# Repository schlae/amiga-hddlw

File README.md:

# Herr Doktor Diskettenlaufwerk (Amiga-HDDLW)

Late-model Amiga computers use customized floppy drives (like the Chinon
FZ-357A) to be able to read and write high-density floppy disks
(colloquially known as 1.44MB floppies, although the Amiga can store 1.76MB
because it packs in four additional sectors per track.)

Why a customized floppy drive? The Amiga custom chip, Paula, only supports
the slower bit rate used by double-density floppy disks. Instead of spending
a bunch of money to change the Paula chip, Commodore engineers got a
customized floppy drive that spun the disk at half speed when it detected
a high-density floppy disk.

In the 1990s, some 3rd party vendors released Amiga compatible floppy drives.
One such design is the AMTRADE "The Real HD-Drive" A357. It uses a modified
Sony MPF920-E or a TEAC FD-235HF (both fairly common) along with a small
adapter circuit board containing a 16V8 PAL.

I've done a bit of reverse engineering to understand how the A357 works,
and I've been able to build a functional replica. It's not an exact copy
because the original PAL is locked. I'm calling it the Herr Doktor
Diskettenlaufwerk, or HDDLW.

*Please note that I have not fabbed out this design yet, and although the
design is tested and expected to work, go forward at your own risk.*

## Fabrication

The board is a simple 2-layer affair with a small handful of parts. The
dimensions are 93.5mm x 20.3mm (3.68" x 0.8").

[Schematic](https://github.com/schlae/amiga-hddlw/blob/main/amiga-hddlw.pdf)

[Bill of Materials](https://github.com/schlae/amiga-hddlw/blob/main/amiga-hddlw.csv)

[Fab Package](https://github.com/schlae/amiga-hddlw/blob/main/fab/amiga-hddlw_rev1.zip)

Install a 20-pin DIP socket in position U1 just in case you have trouble
programming the PAL. All parts, with the exception of J2, J5, and J6, should
be installed on the top side of the board.

J4 should be a Molex 4-pin header with a key. In a pinch, you can sub it out
with a standard 4-pin header but it will be very easy to connect the cable
backwards, which will put 12V on the drive's 5V rail, destroying everything!

Install **either** J5 **or** J6 depending on the drive you plan to use. If you
install both, J5 will interfere with the drive select jumpers on the Sony
drive and potentially damage them.

Jumper J3 should be set to 1 for DF0 and 2 for DF1. Position 3 has not been
tested yet but may work.

## Rework

You will (most likely) need to add a bodge resistor to the design for it to
operate properly on many drives. This is because the pullup on the INDEX line
on the drive itself is weak or nonexistent. Connect a 10K ohm resistor from
pin 7 of the PAL to pin 20 of the PAL.

(Bottom view of the board)

## PAL programming

See the [source file](https://github.com/schlae/amiga-hddlw/blob/main/pal/amiga-hddlw.pld).

The logic equations are assembled using [galette](https://github.com/simon-frankau/galette)
and can be burned to the PAL using a number of different tools. I use the
TL-866 with the [minipro](https://gitlab.com/DavidGriffith/minipro) tool under
Linux, along with the ATF16V8B. The speed grade is not critical.

## Drive modifications

The HDDLW has been tested with the two floppy drives below. It may be possible
to use it with other drives, but you will need to investigate to figure out
the clock connection that sets the motor RPM. You will also need to figure
out how to get the high density select signal onto pin 4 of the drive.

### Sony MPF920-E

Perform the following changes

* Install JC40 (a zero ohm resistor or wire jumper), which is connected to pin
4 of the floppy connector and provides the high-density sense signal. See the
green circle in the image below.
* Cut the trace between pin 38 of IC1 and pin 16 of IC2. This is the motor
driver clock. This is indicated by the diagonal arrow in the image below.
* Connect a wire from pin 38 of IC1 to pin 14 of the floppy connector (blue
wire in the image)
* Connect a wire from pin 16 of IC2 to pin 6 of the floppy connector (red
wire in the image)
* (Optional) This drive *may* have issues regulating the motor speed at lower RPMs. You can try changing resistor R21 (located next to IC2) from 100K to a 68K resistor.

### TEAC FD-235HF

Perform the following changes

* Install S5 (a zero ohm resistor or wire jumper), which is connected to pin 4
of the floppy connector and provides the high-density sense signal (circled in
the image)
* Remove 1K resistor R9 (which may be named differently on different board
revs, but one end is always tied to pin 4 of J5; pointed to by the green
arrow)
* Connect a wire from U1 pin 48 to pin 14 of the floppy connector
* Connect a wire from J5 pin 4 to pin 6 of the floppy connector

TEAC used several different board versions, so your board may not look exactly
alike. The example below uses R12 instead of R9, and S5 has been moved although
it retains the same designator.

Another alternative board uses R12 (as above) but uses S6 instead of S5.

## Functional Explanation

The drive modifications intercept the clock signal that goes between the
floppy drive's main control IC and the motor controller, bringing them out
to two unused pins on the floppy connector. They also enable the undocumented
feature that provides a high-density detect output on pin 4.

The PAL checks for high density disks by looking at pin 4. If a high density
disk is inserted, the PAL

* Divides the motor clock by 2 to slow the RPM from 300 to 150rpm
* Returns the drive ID pattern `10101010...` to the Amiga to let it know that
this is a high-density drive/disk.

If a double-density disk is inserted, the PAL

* Passes the motor clock signal through unchanged so the disk spins at 300rpm
* Returns the drive ID pattern `11111111...`, a double-density drive/disk

And that's about it.

## Troubleshooting

Some folks have issues where high density disks will sometimes read but will not format correctly. This can be caused by the motor speed not regulating well at the lower RPM. On the Sony drive, you can replace R21 with a 68K resistor. The TEAC drives may have similar problems but I haven't figured out a rework for them.

## License
This work is licensed under a Creative Commons Attribution-ShareAlike 4.0
International License. See [https://creativecommons.org/licenses/by-sa/4.0/](https://creativecommons.org/licenses/by-sa/4.0/).

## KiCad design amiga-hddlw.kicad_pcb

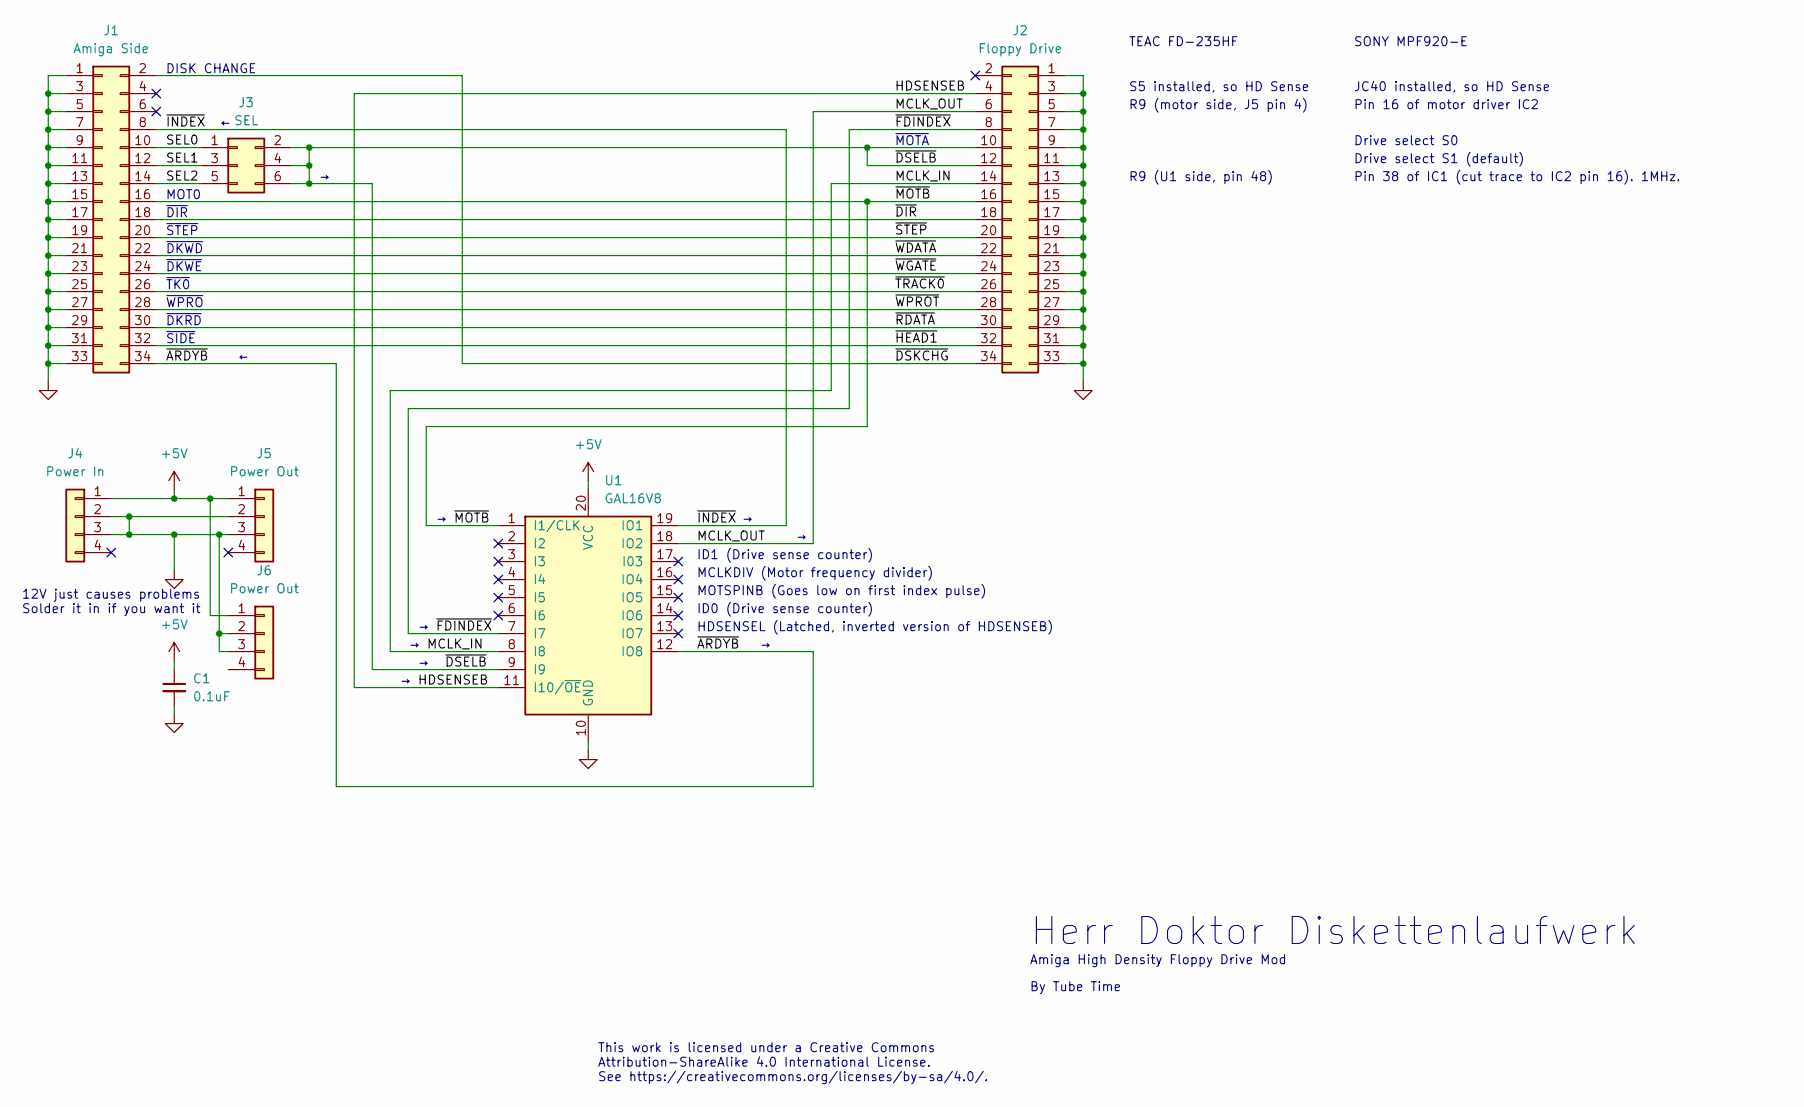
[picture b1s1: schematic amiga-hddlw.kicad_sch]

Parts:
C1: 0.1uF; CAPAC200; Mouser 594-K104K10X7RF53H5 or equiv
J1: Amiga Side; HEADER_2x17_254_SHROUDED; Mouser 737-BHR-34-VUA or equiv
J2: Floppy Drive; PinSocket_2x17_P2.54mm_Vertical; Mouser 517-929975-01-17-RK or equiv
J3: SEL; PinHeader_2x03_P2.54mm_Vertical; Mouser (Just use generic breakaway header)
J4: Power In; PinHeader_1x04_P2.54mm_Vertical; Mouser 571-1718254
J5: Power Out; PinSocket_1x04_P2.54mm_Vertical; Mouser 571-5-146763-6 or equiv
J6: Power Out; PinSocket_1x04_P2.54mm_Vertical
U1: GAL16V8; DIP254P762X635-20; Mouser 556-AF16V8B15PU

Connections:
+5V: C1.1, J4.1, J5.1, J6.1, U1.20 (VCC)
/HDSENSEB: J2.4, U1.11 (I10/~OE)
/MCLK_IN: J2.14, U1.8 (I8)
/MCLK_OUT: J2.6, U1.18 (IO2)
/SEL0: J1.10, J3.1
/SEL1: J1.12, J3.3
/SEL2: J1.14, J3.5
/~ARDYB: J1.34, U1.12 (IO8)
/~DIR: J1.18, J2.18
/~DSELB: J2.10, J2.12, J3.2, J3.4, J3.6, U1.9 (I9)
/~DSKCHG: J1.2, J2.34
/~FDINDEX: J2.8, U1.7 (I7)
/~HEAD1: J1.32, J2.32
/~INDEX: J1.8, U1.19 (IO1)
/~MOTB: J1.16, J2.16, U1.1 (I1/CLK)
/~RDATA: J1.30, J2.30
/~STEP: J1.20, J2.20
/~TRACK0: J1.26, J2.26
/~WDATA: J1.22, J2.22
/~WGATE: J1.24, J2.24
/~WPROT: J1.28, J2.28
GND: C1.2, J1.1, J1.3, J1.5, J1.7, J1.9, J1.11, J1.13, J1.15, J1.17, J1.19, J1.21, J1.23, J1.25, J1.27, J1.29, J1.31, J1.33, J2.1, J2.3, J2.5, J2.7, J2.9, J2.11, J2.13, J2.15, J2.17, J2.19, J2.21, J2.23, J2.25, J2.27, J2.29, J2.31, J2.33, J4.2, J4.3, J5.2, J5.3, J6.2, J6.3, U1.10 (GND)

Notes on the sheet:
DISK CHANGE
~{WPRO}
MOTSPINB (Goes low on first index pulse)
S5 installed, so HD Sense
By Tube Time
MCLKDIV (Motor frequency divider)
HDSENSEL (Latched, inverted version of HDSENSEB)
~{DKWE}
Pin 38 of IC1 (cut trace to IC2 pin 16). 1MHz.
~{STEP}
Amiga High Density Floppy Drive Mod
JC40 installed, so HD Sense
SONY MPF920-E
~{TK0}
Herr Doktor Diskettenlaufwerk
~{DIR}
Drive select S1 (default)
ID0 (Drive sense counter)
R9 (motor side, J5 pin 4)
~{MOTA}
12V just causes problems Solder it in if you want it
Pin 16 of motor driver IC2
~{DKWD}
ID1 (Drive sense counter)
~{DKRD}
Drive select S0
R9 (U1 side, pin 48)
MOT0
This work is licensed under a Creative Commons Attribution-ShareAlike 4.0 International License. See https://creativecommons.org/licenses/by-sa/4.0/.
~{SIDE}
TEAC FD-235HF

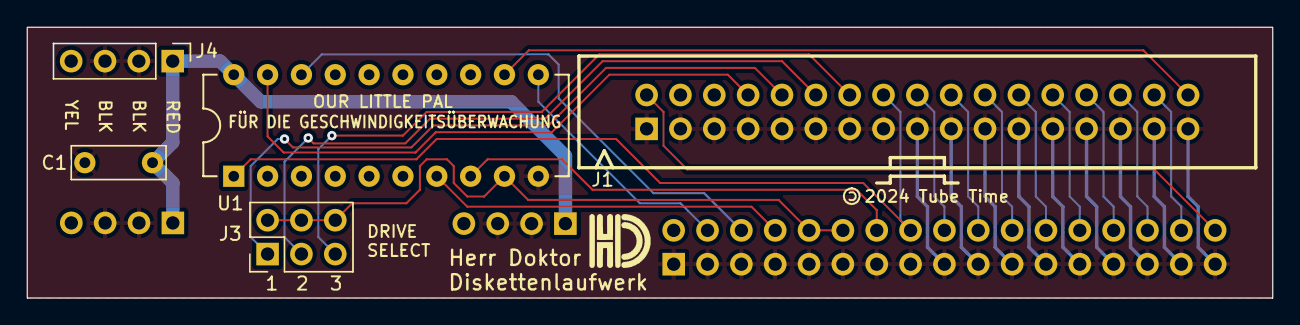
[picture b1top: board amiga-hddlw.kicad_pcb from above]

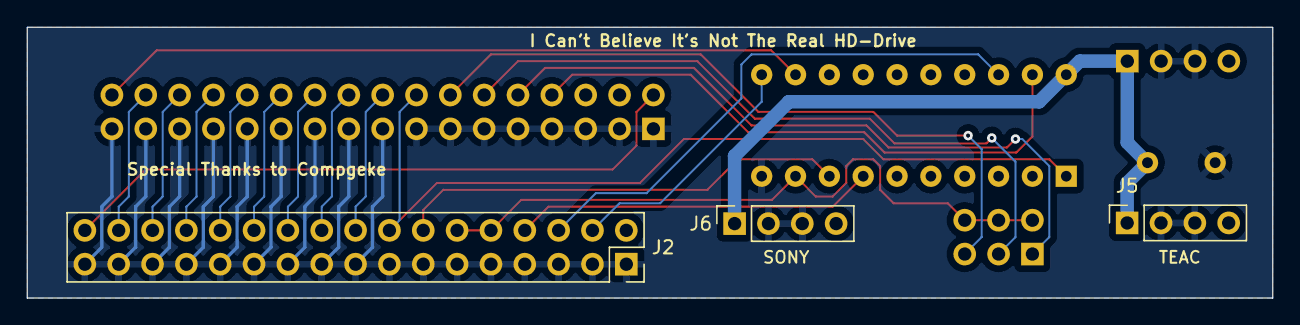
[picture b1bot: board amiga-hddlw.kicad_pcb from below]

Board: 2 copper layers, 93.5 x 20.3 mm, 8 parts (3 on the bottom side), 22 nets.

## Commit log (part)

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2024-04-13 clarify floppy mod zero ohm resistors
2024-05-17 Add JEDEC file
2024-05-18 Add additional Teac variation
2024-12-12 Sony rework for poor speed regulation
